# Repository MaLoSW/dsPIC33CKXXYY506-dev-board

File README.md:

# dsPIC33CKXXYY506-dev-board
Development board for a 64-pin dsPIC33CKXXXYY506 chip (actually I'm using a dsPIC33CK256MC506)

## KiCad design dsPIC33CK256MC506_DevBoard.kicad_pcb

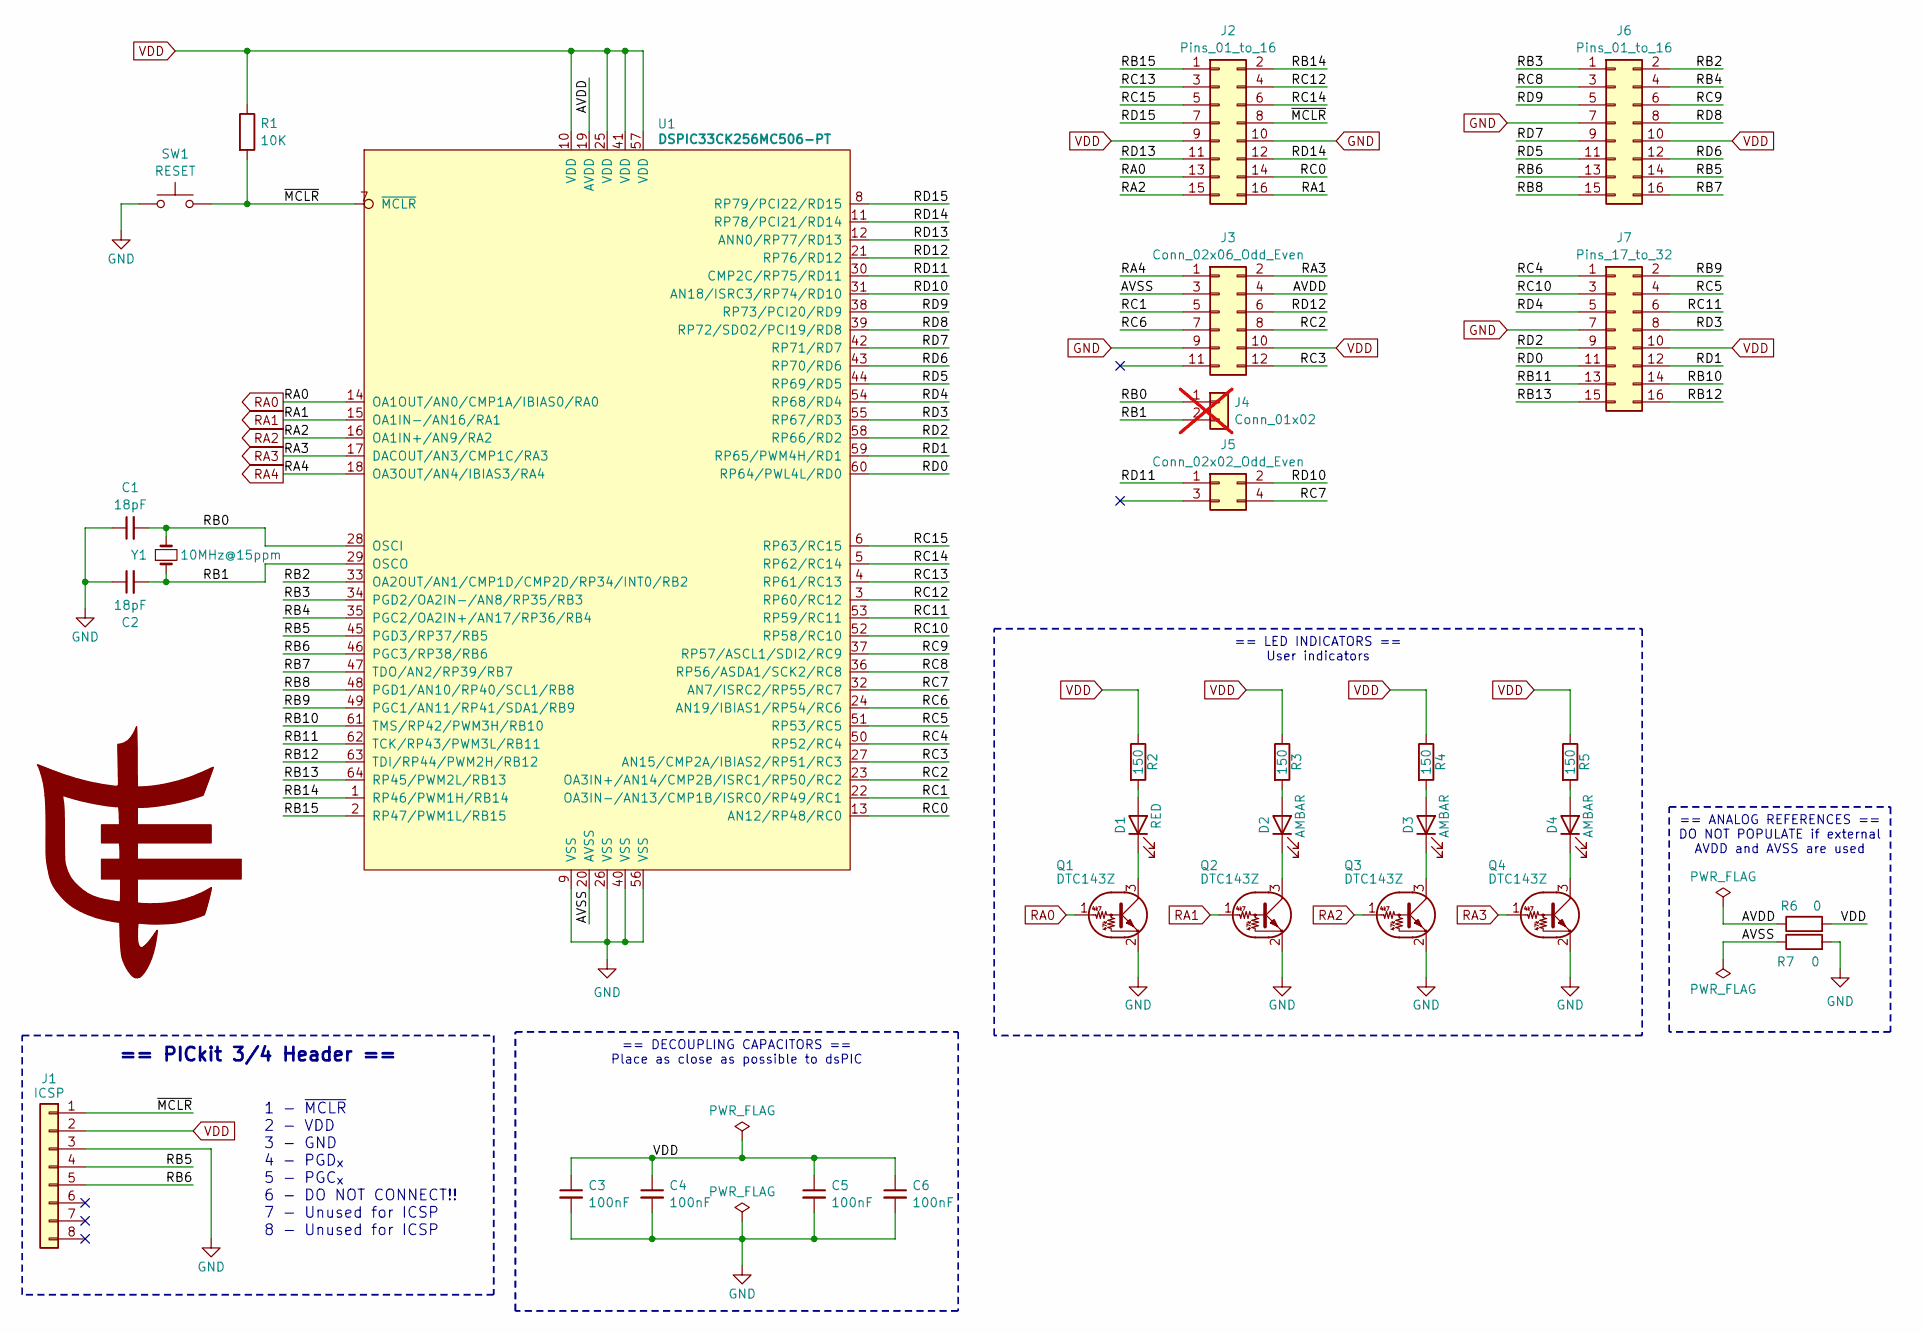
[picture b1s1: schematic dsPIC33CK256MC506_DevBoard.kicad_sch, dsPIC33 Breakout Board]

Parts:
C1, C2: 18pF; C_0603_1608Metric_Pad1.08x0.95mm_HandSolder; MOUSER Part 791-0805N180J500CT
C3, C4, C5, C6: 100nF; C_0603_1608Metric_Pad1.08x0.95mm_HandSolder; MOUSER Part Generic 0603 ceramic capacitor
D1: RED; LED_0805_2012Metric_Pad1.15x1.40mm_HandSolder; MOUSER Part Generic 0805 RED SMD LED
D2, D3, D4: AMBAR; LED_0805_2012Metric_Pad1.15x1.40mm_HandSolder; MOUSER Part Generic 0805 AMBAR SMD LED
J1: ICSP; PinHeader_1x08_P2.54mm_Vertical; MOUSER Part Geneeric 2.54mm(100 mil) single line ma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
J2, J6: Pins_01_to_16; PinHeader_2x08_P2.54mm_Vertical; MOUSER Part Geneeric 2.54mm(100 mil) dual line male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
J3: Conn_02x06_Odd_Even; PinHeader_2x06_P2.54mm_Vertical; MOUSER Part Geneeric 2.54mm(100 mil) dual line male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
J4: Conn_01x02; PinHeader_1x02_P2.54mm_Vertical; MOUSER Part Geneeric 2.54mm(100 mil) single line ma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; not fitted
J5: Conn_02x02_Odd_Even; PinHeader_2x02_P2.54mm_Vertical; MOUSER Part Geneeric 2.54mm(100 mil) dual line male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
J7: Pins_17_to_32; PinHeader_2x08_P2.54mm_Vertical; MOUSER Part Geneeric 2.54mm(100 mil) dual line male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
Q1, Q2, Q3, Q4: DTC143Z; SOT-23_Handsoldering; MOUSER Part 771-PDTC143ZTT/R
R1: 10K; R_0805_2012Metric_Pad1.20x1.40mm_HandSolder; MOUSER Part Generic 0805 SMD resistor
R2, R3, R4, R5: 150; R_0805_2012Metric_Pad1.20x1.40mm_HandSolder; MOUSER Part Generic 0805 SMD resistor
R6, R7: 0; R_0805_2012Metric_Pad1.20x1.40mm_HandSolder; MOUSER Part Generic 0805 SMD resistor
SW1: RESET; SW_SPST_CK_RS282G05A3; MOUSER Part 3x6x2.5mm SMD push button
U1: DSPIC33CK256MC506-PT; TQFP-64_10x10mm_P0.5mm; MOUSER Part 579-D33CK256MC506IPT
Y1: 10MHz@15ppm; Crystal_SMD_HC49-SD; MOUSER Part 669-E1SHA18-10T

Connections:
/AVDD: J3.4, R6.1, U1.19 (AVDD)
/AVSS: J3.3, R7.1, U1.20 (AVSS)
/RB0: C1.2, J4.1, U1.28 (OSCI), Y1.2
/RB1: C2.2, J4.2, U1.29 (OSCO), Y1.1
/RB2: J6.2, U1.33 (OA2OUT/AN1/CMP1D/CMP2D/RP34/INT0/RB2)
/RB3: J6.1, U1.34 (PGD2/OA2IN-/AN8/RP35/RB3)
/RB4: J6.4, U1.35 (PGC2/OA2IN+/AN17/RP36/RB4)
/RB5: J1.4, J6.14, U1.45 (PGD3/RP37/RB5)
/RB6: J1.5, J6.13, U1.46 (PGC3/RP38/RB6)
/RB7: J6.16, U1.47 (TDO/AN2/RP39/RB7)
/RB8: J6.15, U1.48 (PGD1/AN10/RP40/SCL1/RB8)
/RB9: J7.2, U1.49 (PGC1/AN11/RP41/SDA1/RB9)
/RB10: J7.14, U1.61 (TMS/RP42/PWM3H/RB10)
/RB11: J7.13, U1.62 (TCK/RP43/PWM3L/RB11)
/RB12: J7.16, U1.63 (TDI/RP44/PWM2H/RB12)
/RB13: J7.15, U1.64 (RP45/PWM2L/RB13)
/RB14: J2.2, U1.1 (RP46/PWM1H/RB14)
/RB15: J2.1, U1.2 (RP47/PWM1L/RB15)
/RC0: J2.14, U1.13 (AN12/RP48/RC0)
/RC1: J3.5, U1.22 (OA3IN-/AN13/CMP1B/ISRC0/RP49/RC1)
/RC2: J3.8, U1.23 (OA3IN+/AN14/CMP2B/ISRC1/RP50/RC2)
/RC3: J3.12, U1.27 (AN15/CMP2A/IBIAS2/RP51/RC3)
/RC4: J7.1, U1.50 (RP52/RC4)
/RC5: J7.4, U1.51 (RP53/RC5)
/RC6: J3.7, U1.24 (AN19/IBIAS1/RP54/RC6)
/RC7: J5.4, U1.32 (AN7/ISRC2/RP55/RC7)
/RC8: J6.3, U1.36 (RP56/ASDA1/SCK2/RC8)
/RC9: J6.6, U1.37 (RP57/ASCL1/SDI2/RC9)
/RC10: J7.3, U1.52 (RP58/RC10)
/RC11: J7.6, U1.53 (RP59/RC11)
/RC12: J2.4, U1.3 (RP60/RC12)
/RC13: J2.3, U1.4 (RP61/RC13)
/RC14: J2.6, U1.5 (RP62/RC14)
/RC15: J2.5, U1.6 (RP63/RC15)
/RD0: J7.11, U1.60 (RP64/PWL4L/RD0)
/RD1: J7.12, U1.59 (RP65/PWM4H/RD1)
/RD2: J7.9, U1.58 (RP66/RD2)
/RD3: J7.8, U1.55 (RP67/RD3)
/RD4: J7.5, U1.54 (RP68/RD4)
/RD5: J6.11, U1.44 (RP69/RD5)
/RD6: J6.12, U1.43 (RP70/RD6)
/RD7: J6.9, U1.42 (RP71/RD7)
/RD8: J6.8, U1.39 (RP72/SDO2/PCI19/RD8)
/RD9: J6.5, U1.38 (RP73/PCI20/RD9)
/RD10: J5.2, U1.31 (AN18/ISRC3/RP74/RD10)
/RD11: J5.1, U1.30 (CMP2C/RP75/RD11)
/RD12: J3.6, U1.21 (RP76/RD12)
/RD13: J2.11, U1.12 (ANN0/RP77/RD13)
/RD14: J2.12, U1.11 (RP78/PCI21/RD14)
/RD15: J2.7, U1.8 (RP79/PCI22/RD15)
/~MCLR: J1.1, J2.8, R1.2, SW1.2, U1.7 (~MCLR)
GND: C1.1, C2.1, C3.2, C4.2, C5.2, C6.2, J1.3, J2.10, J3.9, J6.7, J7.7, Q1.2 (E), Q2.2 (E), Q3.2 (E), Q4.2 (E), R7.2, SW1.1, U1.9 (VSS), U1.26 (VSS), U1.40 (VSS), U1.56 (VSS)
unnamed: D1.2 (A), R2.2
unnamed: D1.1 (K), Q1.3 (C)
unnamed: D2.2 (A), R3.2
unnamed: D2.1 (K), Q2.3 (C)
unnamed: D3.2 (A), R4.2
unnamed: D3.1 (K), Q3.3 (C)
unnamed: D4.2 (A), R5.2
unnamed: D4.1 (K), Q4.3 (C)
RA0: J2.13, Q1.1 (B), U1.14 (OA1OUT/AN0/CMP1A/IBIAS0/RA0)
RA1: J2.16, Q2.1 (B), U1.15 (OA1IN-/AN16/RA1)
RA2: J2.15, Q3.1 (B), U1.16 (OA1IN+/AN9/RA2)
RA3: J3.2, Q4.1 (B), U1.17 (DACOUT/AN3/CMP1C/RA3)
RA4: J3.1, U1.18 (OA3OUT/AN4/IBIAS3/RA4)
VDD: C3.1, C4.1, C5.1, C6.1, J1.2, J2.9, J3.10, J6.10, J7.10, R1.1, R2.1, R3.1, R4.1, R5.1, R6.2, U1.10 (VDD), U1.25 (VDD), U1.41 (VDD), U1.57 (VDD)

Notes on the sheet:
== LED INDICATORS == User indicators
== PICkit 3/4 Header ==
== DECOUPLING CAPACITORS == Place as close as possible to dsPIC
== ANALOG REFERENCES == DO NOT POPULATE if external AVDD and AVSS are used
1 - ~{MCLR} 2 - VDD 3 - GND 4 - PGD_{x} 5 - PGC_{x} 6 - DO NOT CONNECT!! 7 - Unused for ICSP 8 - Unused for ICSP

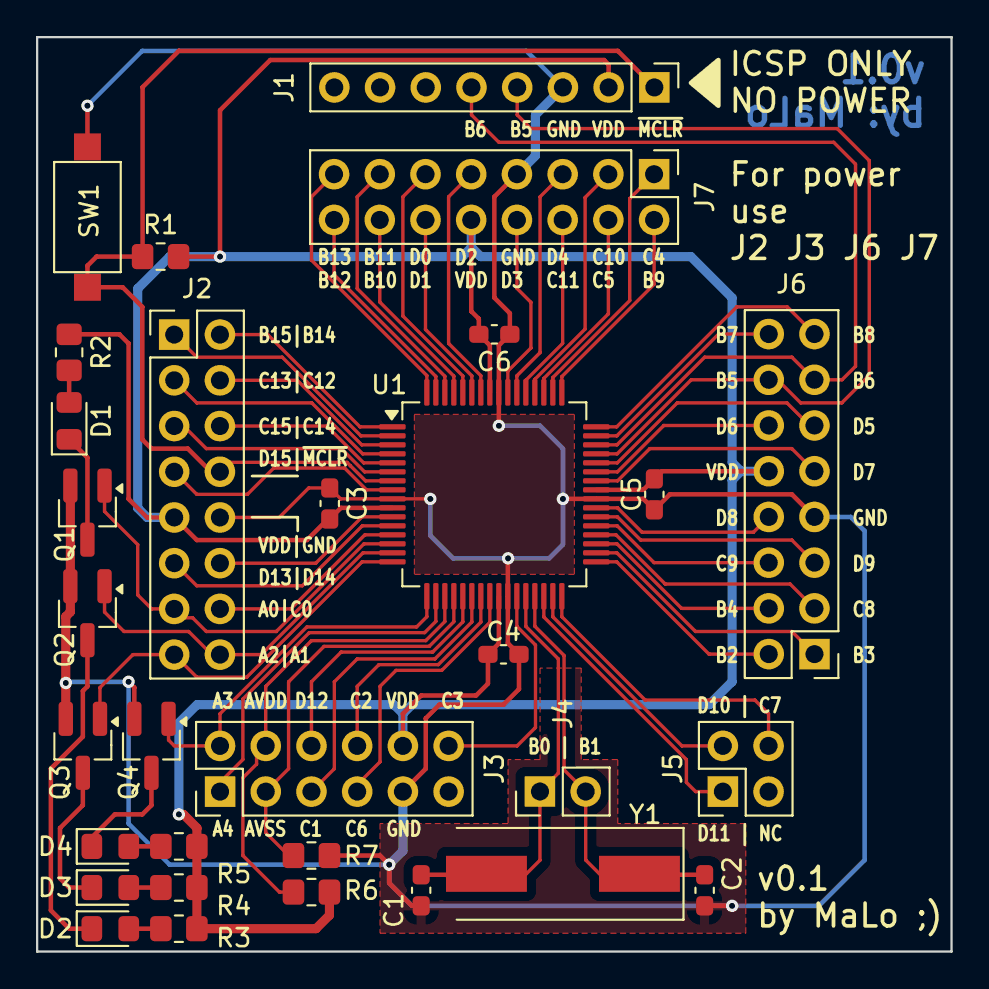
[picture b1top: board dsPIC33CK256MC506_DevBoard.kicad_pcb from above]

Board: 2 copper layers, 50.8 x 50.8 mm, 31 parts (0 on the bottom side), 66 nets.

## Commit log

2024-08-31 Initial PCB sent to fabrication
2024-09-17 Updated schematic according to actual board
2024-09-18 Updated documentation and component values
    - Schematic for analyzing
    - Schematic for printing
    - Interactive BOM for assembly
    - Updated component values
